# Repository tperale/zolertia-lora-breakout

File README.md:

# LoRa Breakout board for the Zolertia RE-Mote Rev-B

## Schematics

## BOM

| Reference | Value           | Footprint                                                         | Datasheet                                                                     | Link                                                               |
|-----------|-----------------|-------------------------------------------------------------------|-------------------------------------------------------------------------------|--------------------------------------------------------------------|
| U1        | RFM95W-868S2    | RF_Module.pretty:HOPERF_RFM9XW_SMD                                | [rfm95](https://www.hoperf.com/data/upload/portal/20181127/5bfcbea20e9ef.pdf) | [rs](https://befr.rs-online.com/web/p/rf-modules/1251259/)         |
| J2        | Conn_Coaxial    | Connector_Coaxial.pretty:SMA_Amphenol_132289_EdgeMount            | ~                                                                             | [rs](https://befr.rs-online.com/web/p/coaxial-connectors/1440918/) |
| J3        | Conn_01x18_Male | Connector_PinHeader_2.54mm.pretty:PinHeader_1x18_P2.54mm_Vertical | ~                                                                             | [rs](https://befr.rs-online.com/web/p/pcb-headers/8281620/)        |
| J4        | Conn_Coaxial    | Connector_Coaxial.pretty:U.FL_Molex_MCRF_73412-0110_Vertical      | ~                                                                             | ~                                                                  |
| SW1       | SW_Push         | Button_Switch_SMD.pretty:SW_DIP_6.7x4.1mm_W8.61mm_P2.54mm         | ~                                                                             | ~                                                                  |
| C1        | 10uF            | Capacitor_SMD:C_1206_3216Metric_Pad1.33x1.80mm_HandSolder         | ~                                                                             | ~                                                                  |
| C2        | 1uF             | Capacitor_SMD:C_1206_3216Metric_Pad1.33x1.80mm_HandSolder         | ~                                                                             | ~                                                                  |
| R1        | 220R            | Resistor_SMD:R_1206_3216Metric_Pad1.30x1.75mm_HandSolder          | ~                                                                             | ~                                                                  |
| R2        | 10KR            | Resistor_SMD:R_1206_3216Metric_Pad1.30x1.75mm_HandSolder          | ~                                                                             | ~                                                                  |
## Credits

### 3D Models

* [Amphenol Right Angle Edge Mount SMA Connector](https://grabcad.com/library/amphenol-right-angle-edge-mount-sma-connector-1)
* [RFM95 LoRa Radio Module](https://grabcad.com/library/rfm95-lora-radio-module-1)

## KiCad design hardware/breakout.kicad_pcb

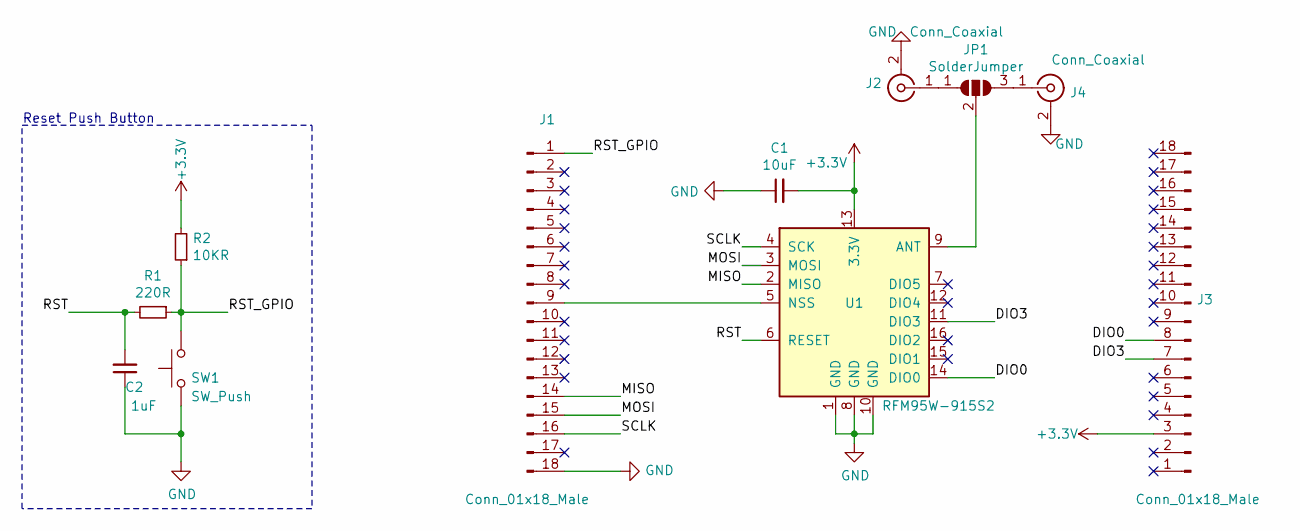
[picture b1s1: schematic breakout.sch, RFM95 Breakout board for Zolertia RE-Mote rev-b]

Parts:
C1: 10uF; C_1206_3216Metric_Pad1.33x1.80mm_HandSolder
C2: 1uF; C_1206_3216Metric_Pad1.33x1.80mm_HandSolder
J1, J3: Conn_01x18_Male; PinHeader_1x18_P2.54mm_Vertical
J2: Conn_Coaxial; SMA_Samtec_SMA-J-P-X-ST-EM1_EdgeMount
J4: Conn_Coaxial; U.FL_Molex_MCRF_73412-0110_Vertical
JP1: SolderJumper; SolderJumper-3_P1.3mm_Open_RoundedPad1.0x1.5mm
R1: 220R; R_1206_3216Metric_Pad1.30x1.75mm_HandSolder
R2: 10KR; R_1206_3216Metric_Pad1.30x1.75mm_HandSolder
SW1: SW_Push; SW_DIP_SPSTx01_Slide_6.7x4.1mm_W8.61mm_P2.54mm_LowProfile
U1: RFM95W-915S2; HOPERF_RFM9XW_SMD

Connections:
+3V3: C1.2, J3.3, R2.2, U1.13 (3.3V)
/DIO0: J3.8, U1.14 (DIO0)
/DIO3: J3.7, U1.11 (DIO3)
/MISO: J1.14, U1.2 (MISO)
/MOSI: J1.15, U1.3 (MOSI)
/RST: C2.2, R1.2, U1.6 (RESET)
/RST_GPIO: J1.1, R1.1, R2.1, SW1.2
/SCLK: J1.16, U1.4 (SCK)
GND: C1.1, C2.1, J1.18, J2.2 (Ext), J4.2 (Ext), SW1.1, U1.1 (GND), U1.8 (GND), U1.10 (GND)
unnamed: J1.9, U1.5 (NSS)
unnamed: J2.1 (In), JP1.1 (A)
unnamed: J4.1 (In), JP1.3 (B)
unnamed: JP1.2 (C), U1.9 (ANT)

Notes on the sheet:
Reset Push Button

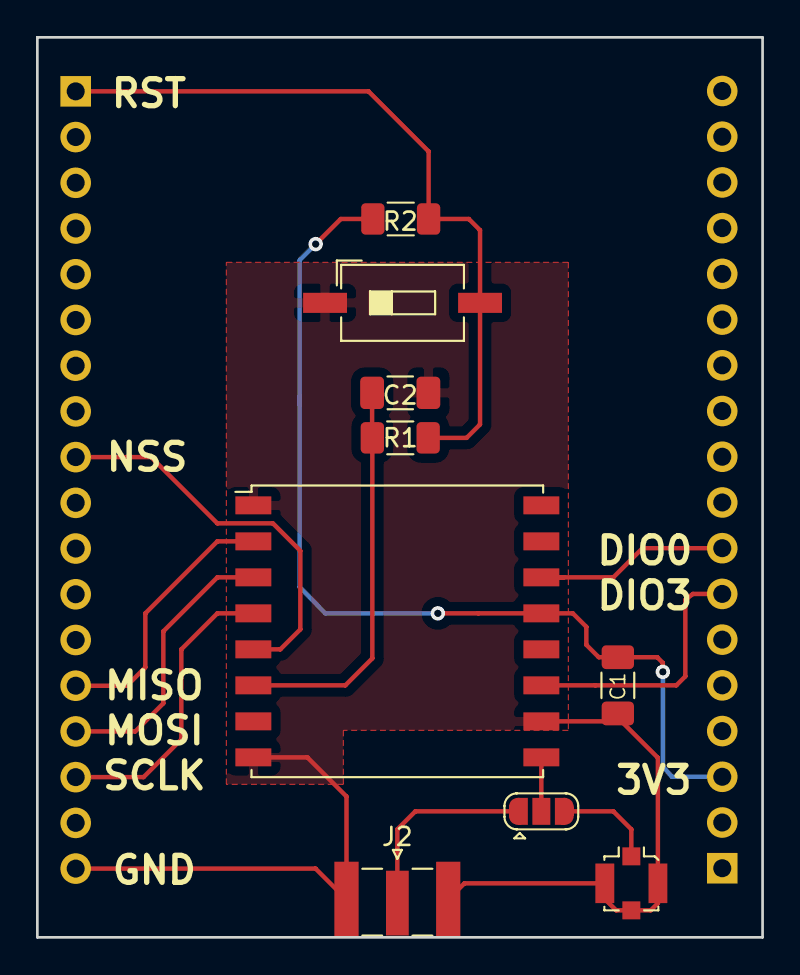
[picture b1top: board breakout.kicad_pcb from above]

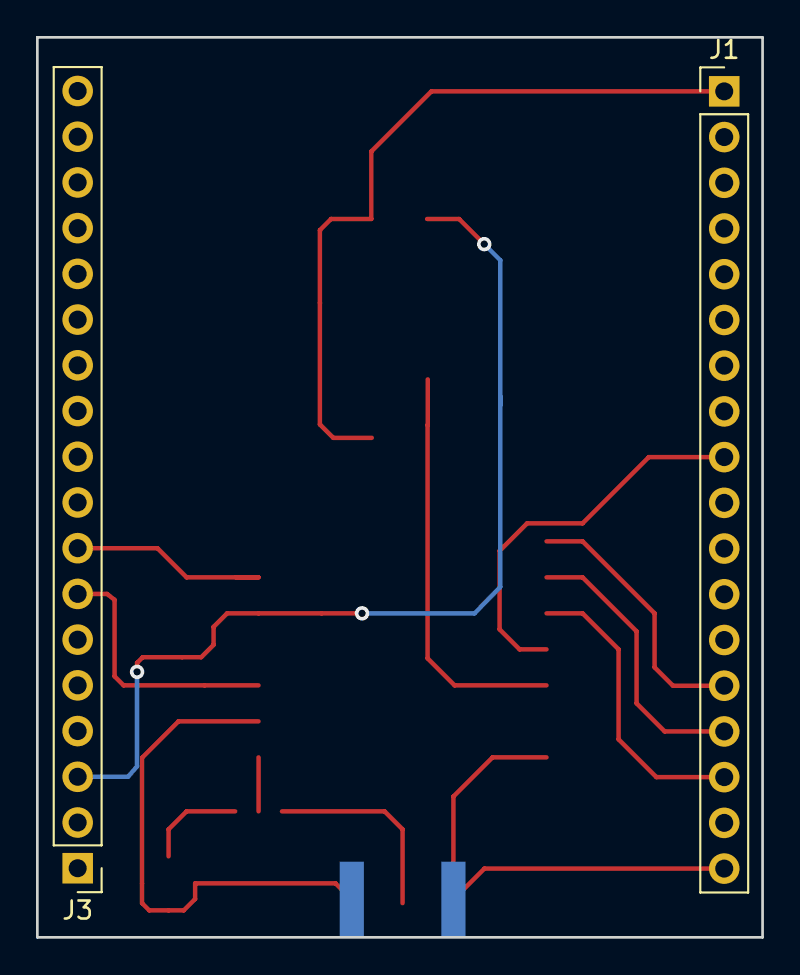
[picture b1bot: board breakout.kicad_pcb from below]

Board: 2 copper layers, 40.3 x 50.0 mm, 11 parts (2 on the bottom side), 13 nets.

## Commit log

2020-10-09 Create pcb
2020-10-09 Documentation
2020-10-13 [enh] The complete outline is overkill
2020-10-13 [add] Complete 3D models
2020-10-13 [add] 3D model for antenna
2020-10-13 [add] Push button for manual rseet
2020-10-13 Update rendering
2020-10-13 [fix] Hide preview of antenna
2020-10-14 [add] Debouncing circuit
2020-10-19 [fix] fixed board size + 3v3 input + reset button
2020-10-19 Last quick modification
2020-10-19 [add] Images
2021-04-08 add NSS symbol to silkscreen
2021-04-09 fix the footprint of the antenna connector
